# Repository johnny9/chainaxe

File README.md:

# Chainaxe

ESP32-S3 replacement control board for Antminer S19 hashboards. It drops into the stock
control-board position: the outline, mounting holes and connector positions follow a measured
drawing of the original S19 controller, and it talks to up to three hashboards over the standard
18-pin data cables.

## Board at a glance

- 110 x 100 mm, 6 layers, 1.6 mm, ENIG
- ESP32-S3-WROOM-1 (N16R8); console and flashing over native USB-C
- 3 hashboard data headers (2x9, 2.0 mm), one ESP32 UART each, plus shared I2C
- 4 fan headers (4.2 mm 2x2, or 2.54 mm 4-pin), PWM driven directly from the ESP32 and tach
  read back through PCNT
- 12 V input with reverse protection; 12 V fan bus and ground return as copper pours
- Antminer PSU control header (I2C + PSU_EN)
- On-board 3.3 V from a TPSM861253 buck module
- RESET and BOOT buttons for development

Full pinout, GPIO map and design notes: [boards/chainaxe/README.md](boards/chainaxe/README.md).

## Repository layout

| Path | What |
|---|---|
| `boards/chainaxe/` | KiCad project (schematic, PCB, local symbol and footprint libraries) |
| `mfg/assembly/` | BOM and pick-and-place files for assembly |
| `extra/outline/` | Measured S19 control-board drawing and the board outline DXF |
| `extra/axe_logo/` | Generator for the Chainaxe silkscreen icon |
| `extra/scripts/` | Helper scripts used while building the board |
| `docs/images/` | Board renders |

## Bottom

## Licence

Licensed under the CERN Open Hardware Licence Version 2 - Strongly Reciprocal
(CERN-OHL-S-2.0); see [LICENSE](LICENSE).

## Credits

Derived from [skot/bitcrane](https://github.com/skot/bitcrane) for the hashboard interface (used
under CERN-OHL-S-2.0 with the author's permission) and
[bitaxeorg/BitaxeGT](https://github.com/bitaxeorg/BitaxeGT) for the ESP32-S3 section.

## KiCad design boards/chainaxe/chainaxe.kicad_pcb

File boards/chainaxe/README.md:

# Chainaxe control board v0.1

ESP32-S3 Antminer hashboard controller. Outline, mounting holes and connector positions follow a
measured drawing of the stock S19 control board (110 x 100 mm, 6 layers; see extra/outline/),
with a BitaxeGT-style ESP32-S3-WROOM-1 in place of the Bitcrane's FTDI USB bridge.

Derived from [skot/bitcrane](https://github.com/skot/bitcrane) and
[bitaxeorg/BitaxeGT](https://github.com/bitaxeorg/BitaxeGT). Licensed CERN-OHL-S-2.0 (see the
LICENSE at the repository root).

## Connectors (same places as the stock S19 control board)

| Ref | What |
|---|---|
| J2 / J9 / J10 | Hashboard 0 / 1 / 2 data cable, Antminer 18-pin 2x9 2.0 mm |
| J4-J7, J14-J17 | Fans 1-4, 2.54 mm 4-pin or 4.2 mm 2x2 (populate one per fan) |
| J3 | 12 V in (6-pin 4.2 mm), reverse-protected by Q1 (NTMFS002P03P8Z, 1.4 mOhm) |
| J1 | Antminer PSU control, 2x3 2.0 mm (I2C + PSU_EN) |
| J11 | USB-C: ESP32-S3 native USB (flashing + console). Does not power the board. |

## ESP32-S3 GPIO map

Three hashboard UARTs: UART0, UART1 and UART2 routed through the GPIO matrix to any pins below.
The console is on USB-Serial-JTAG, so UART0's default pins (GPIO43/44) are left unused.

| Signal | GPIO | Signal | GPIO |
|---|---|---|---|
| HB0 TX | 48 | HB1 TX | 11 |
| HB0 RX | 47 | HB1 RX | 12 |
| HB0 RST | 14 | HB1 RST | 13 |
| HB0 PLUG | 21 | HB1 PLUG | 10 |
| HB2 TX | 39 | I2C SDA | 9 |
| HB2 RX | 40 | I2C SCL | 3 |
| HB2 RST | 41 | | |
| HB2 PLUG | 38 | PSU_EN | 18 |
| BOOT | 0 | USB D-/D+ | 19 / 20 |

| Fan | PWM GPIO (LEDC) | Tach GPIO (PCNT) |
|---|---|---|
| 1 | 15 | 42 |
| 2 | 16 | 44 |
| 3 | 17 | 2 |
| 4 | 8 | 1 |

The I2C bus is shared by the three hashboard headers and the PSU header. Each slot's A2-A0
straps (pins 6-8) are tied differently (slot 0 = 000, 1 = 001, 2 = 010) so the hashboards answer
at different addresses. The Bitcrane gives each hashboard its own bus through a PCA9546 instead.

Fans are driven directly: each fan's PWM pin is pulled low by a 2N7002K (Q2-Q5) whose gate the
ESP32 drives with 25 kHz LEDC PWM (inverted: gate high = PWM low). A 100k pull-down holds each gate
off, so with the ESP32 in reset the fans' own pull-ups run them at full speed. Tach lines keep
their 36k pull-ups and reach the ESP32 through 1k series resistors; count them with PCNT
(2 pulses per revolution). The ESP-to-fan lines run on the In2 (3V3 plane) layer.

## Power

12 V -> Q1 reverse protection (about 0.3 W at 12 A of fan load, drain tab stitched to a B.Cu
heat spreader) -> TPSM861253 module -> 3V3 (1 A) on the In2 plane.

Stackup: 6 layers (F.Cu signal, In1 GND, In2 3V3, In3 GND, In4 GND, B.Cu signal), the fab's
JLC06161H-3313 build.
Hashboard header pin 16 gets 3V3, as on the Bitcrane.

## Not yet checked on hardware

- Hashboard UARTs are driven straight at 3.3 V, the same as the Bitcrane does from its FTDI.
- Fan PWM pull-ups (R22, R23, R47, R48) go to 3V3. The Bitcrane has none: its EMC2305 drives the
  fans' PWM pins directly and relies on the fans' own pull-ups. They can be left unfitted.
- The shared hashboard I2C bus relies on the slot straps for unique addresses.
- GPIO44 (fan 2 tach) is UART0 RX at boot; harmless as an input.

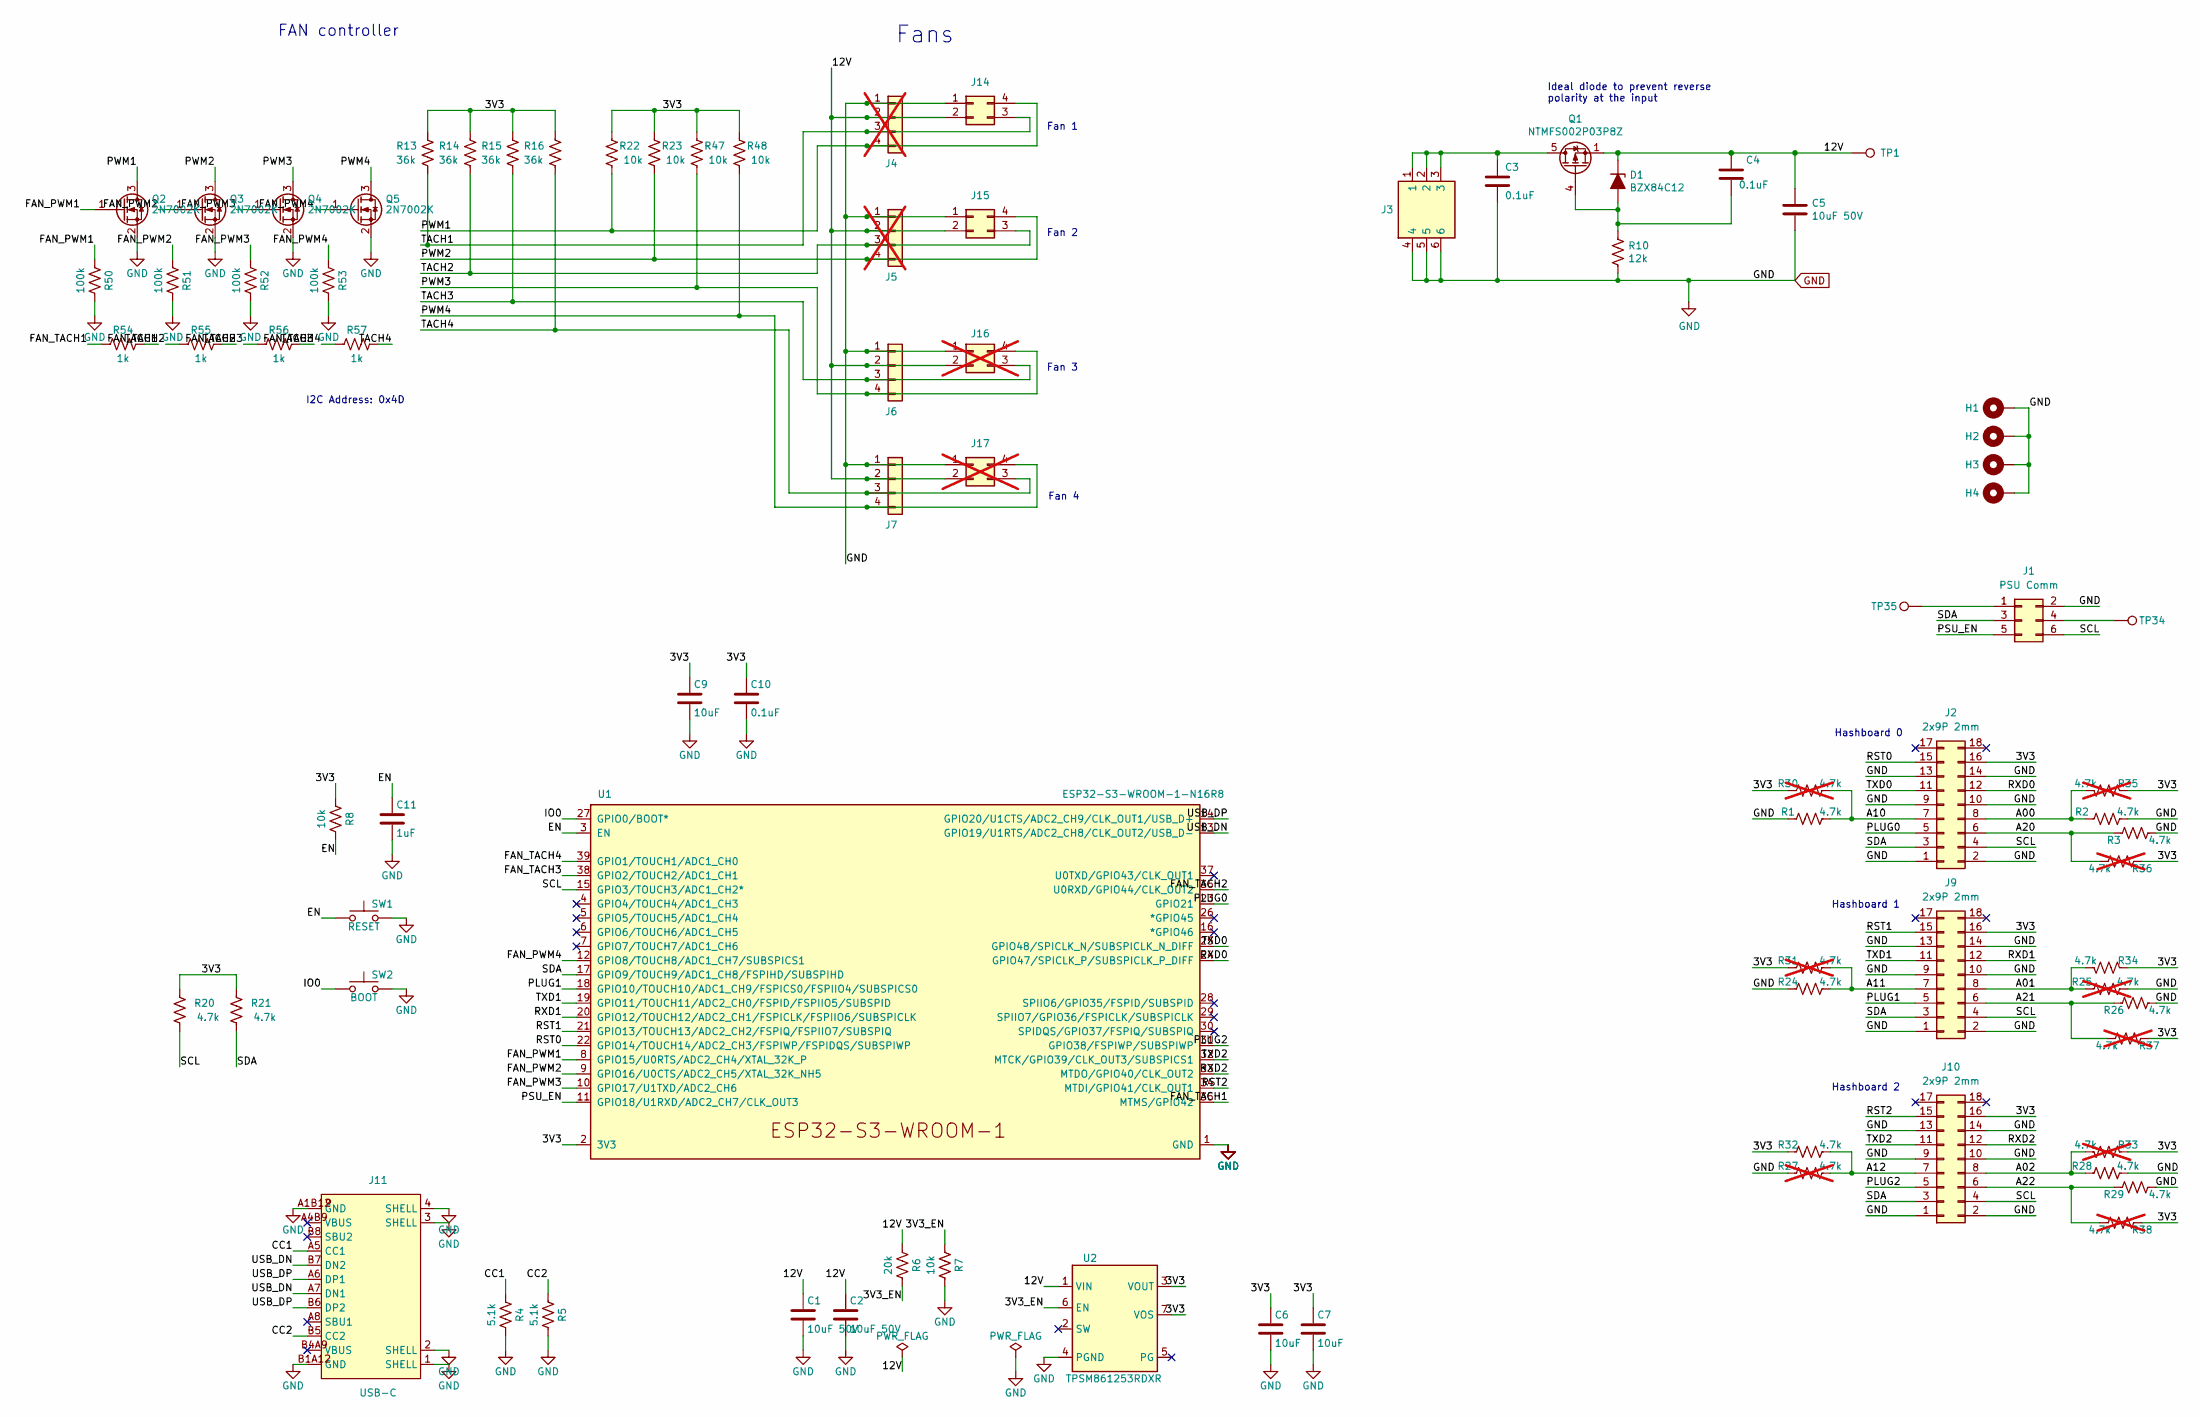
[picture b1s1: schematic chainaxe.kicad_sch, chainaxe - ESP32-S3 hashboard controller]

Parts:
C1, C2, C5: 10uF 50V; C_0805_2012Metric; MPN GRM21BR61H106KE43L; LCSC C440198
C3, C4: 0.1uF; C_0805_2012Metric; MPN CL21B104KCFNNNE; LCSC C28233
C6, C7, C9: 10uF; C_0805_2012Metric; MPN CL21A106KAYNNNE; LCSC C15850
C10: 0.1uF; C_0805_2012Metric; MPN CC0805KRX7R9BB104; LCSC C49678
C11: 1uF; C_0805_2012Metric; MPN CL21B105KBFNNNE; LCSC C28323
D1: BZX84C12; SOT-23-3_L2.9-W1.6-P1.90-LS2.8-BR; MPN BZX84C12; LCSC C19077471
H1, H2, H3, H4: MountingHole_Pad; MountingHole_3mm_Pad
J1: PSU Comm; CONN-TH_6P-P2.00_PHD-2X3A; MPN HC-PHD-2*3A; LCSC C2845614
J2, J9, J10: 2x9P 2mm; CONN-TH_X2026WV-2-09D-46SN; MPN M2026V-2x9P; LCSC C492586
J3: 0455580003; CONN-TH_50362462; MPN 50362462; LCSC C492365
J4, J5: 61900411021; CONN-TH_4P-P2.54_HCTL_HC-2510-4AW; MPN HC-2510-4AW; LCSC C2982043; not fitted
J6, J7: 61900411021; CONN-TH_4P-P2.54_HCTL_HC-2510-4AW; MPN HC-2510-4AW; LCSC C2982043
J11: USB-C; USB-C-SMD_G-SWITCH_GT-USB-7010ASV; MPN GT-USB-7010ASV; LCSC C2988369
J14, J15: 0353180420; CONN-TH_4P-P4.20_5557-2X2AW; MPN 4.2-2*2AW; LCSC C54909
J16, J17: 0353180420; CONN-TH_4P-P4.20_5557-2X2AW; MPN 4.2-2*2AW; LCSC C54909; not fitted
Q1: NTMFS002P03P8Z; onsemi_DFN5_5x6_SO-8FL; MPN NTMFS002P03P8ZT1G; LCSC C2902170
Q2, Q3, Q4, Q5: 2N7002K; SOT-23; MPN 2N7002K; LCSC C22379475
R1, R2, R3, R20, R21, R24, R26, R28, R29, R32, R34: 4.7k; R_0805_2012Metric; MPN 0805W8F4701T5E; LCSC C17673
R4, R5: 5.1k; R_0805_2012Metric; MPN 0805W8F5101T5E; LCSC C27834
R6: 20k; R_0805_2012Metric; MPN 0805W8F2002T5E; LCSC C4328
R7, R8, R22, R23, R47, R48: 10k; R_0805_2012Metric; MPN 0805W8F1002T5E; LCSC C17414
R10: 12k; R_0805_2012Metric; MPN 0805W8F1202T5E; LCSC C17444
R13, R14, R15, R16: 36k; R_0805_2012Metric; MPN 0805W8F3602T5E; LCSC C4360
R25, R27, R30, R31, R33, R35, R36, R37, R38: 4.7k; R_0805_2012Metric; MPN 0805W8F4701T5E; LCSC C17673; not fitted
R50, R51, R52, R53: 100k; R_0805_2012Metric; MPN 0805W8F1003T5E; LCSC C149504
R54, R55, R56, R57: 1k; R_0805_2012Metric; MPN 0805W8F1001T5E; LCSC C17513
SW1: RESET; SW_Push_1P1T_XKB_TS-1187A; MPN TS-1187A-B-A-B; LCSC C318884
SW2: BOOT; SW_Push_1P1T_XKB_TS-1187A; MPN TS-1187A-B-A-B; LCSC C318884
TP1, TP34, TP35: TestPoint; TestPoint_Pad_D1.5mm
U1: ESP32-S3-WROOM-1-N16R8; ESP32-S3-WROOM-1; MPN ESP32-S3-WROOM-1-N16R8; LCSC C2913202
U2: TPSM861253RDXR; TPSM863257RDX; MPN TPSM861253RDXR; LCSC C31183817

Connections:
/3V3: C6.1, C7.1, C9.1, C10.1, J2.16, J9.16, J10.16, R8.1, R13.1, R14.1, R15.1, R16.1, R20.2, R21.2, R22.2, R23.2, R30.1, R31.1, R32.1, R33.1, R34.1, R35.1, R36.1, R37.1, R38.1, R47.2, R48.2, U1.2 (3V3), U2.3 (VOUT), U2.7 (VOS)
/3V3_EN: R6.2, R7.1, U2.6 (EN)
/12V: C1.1, C2.1, C4.1, C5.1, D1.3 (K), J4.2, J5.2, J6.2, J7.2, J14.2, J15.2, J16.2, J17.2, Q1.1 (S), Q1.2 (S), Q1.3 (S), R6.1, TP1.1, U2.1 (VIN)
/A00: J2.8, R2.1, R35.2
/A01: J9.8, R25.1, R34.2
/A02: J10.8, R28.1, R33.2
/A10: J2.7, R1.2, R30.2
/A11: J9.7, R24.2, R31.2
/A12: J10.7, R27.2, R32.2
/A20: J2.6, R3.1, R36.2
/A21: J9.6, R26.1, R37.2
/A22: J10.6, R29.1, R38.2
/CC1: J11.A5 (CC1), R4.1
/CC2: J11.B5 (CC2), R5.1
/EN: C11.1, R8.2, SW1.1, U1.3 (EN)
/FAN_PWM1: Q2.1 (G), R50.1, U1.8 (GPIO15/U0RTS/ADC2_CH4/XTAL_32K_P)
/FAN_PWM2: Q3.1 (G), R51.1, U1.9 (GPIO16/U0CTS/ADC2_CH5/XTAL_32K_NH5)
/FAN_PWM3: Q4.1 (G), R52.1, U1.10 (GPIO17/U1TXD/ADC2_CH6)
/FAN_PWM4: Q5.1 (G), R53.1, U1.12 (GPIO8/TOUCH8/ADC1_CH7/SUBSPICS1)
/FAN_TACH1: R54.1, U1.35 (MTMS/GPIO42)
/FAN_TACH2: R55.1, U1.36 (U0RXD/GPIO44/CLK_OUT2)
/FAN_TACH3: R56.1, U1.38 (GPIO2/TOUCH2/ADC1_CH1)
/FAN_TACH4: R57.1, U1.39 (GPIO1/TOUCH1/ADC1_CH0)
/IO0: SW2.1, U1.27 (GPIO0/BOOT*)
/PLUG0: J2.5, U1.23 (GPIO21)
/PLUG1: J9.5, U1.18 (GPIO10/TOUCH10/ADC1_CH9/FSPICS0/FSPIIO4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)
/PLUG2: J10.5, U1.31 (GPIO38/FSPIWP/SUBSPIWP)
/PSU_EN: J1.5, U1.11 (GPIO18/U1RXD/ADC2_CH7/CLK_OUT3)
/PWM1: J4.4, J14.4, Q2.3 (D), R22.1
/PWM2: J5.4, J15.4, Q3.3 (D), R23.1
/PWM3: J6.4, J16.4, Q4.3 (D), R47.1
/PWM4: J7.4, J17.4, Q5.3 (D), R48.1
/RST0: J2.15, U1.22 (GPIO14/TOUCH14/ADC2_CH3/FSPIWP/FSPIDQS/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)
/RST1: J9.15, U1.21 (GPIO13/TOUCH13/ADC2_CH2/FSPIQ/FSPIIO7/S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)
/RST2: J10.15, U1.34 (MTDI/GPIO41/CLK_OUT1)
/RXD0: J2.12, U1.24 (GPIO47/SPICLK_P/SUBSPICLK_P_DIFF)
/RXD1: J9.12, U1.20 (GPIO12/TOUCH12/ADC2_CH1/FSPICLK/FSPIIO6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)
/RXD2: J10.12, U1.33 (MTDO/GPIO40/CLK_OUT2)
/SCL: J1.6, J2.4, J9.4, J10.4, R20.1, U1.15 (GPIO3/TOUCH3/ADC1_CH2*)
/SDA: J1.3, J2.3, J9.3, J10.3, R21.1, U1.17 (GPIO9/TOUCH9/ADC1_CH8/FSPIHD/SUBSPIHD)
/TACH1: J4.3, J14.3, R13.2, R54.2
/TACH2: J5.3, J15.3, R14.2, R55.2
/TACH3: J6.3, J16.3, R15.2, R56.2
/TACH4: J7.3, J17.3, R16.2, R57.2
/TXD0: J2.11, U1.25 (GPIO48/SPICLK_N/SUBSPICLK_N_DIFF)
/TXD1: J9.11, U1.19 (GPIO11/TOUCH11/ADC2_CH0/FSPID/FSPIIO5/S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)
/TXD2: J10.11, U1.32 (MTCK/GPIO39/CLK_OUT3/SUBSPICS1)
/USB_DN: J11.A7 (DN1), J11.B7 (DN2), U1.13 (GPIO19/U1RTS/ADC2_CH8/CLK_OUT2/USB_D-)
/USB_DP: J11.A6 (DP1), J11.B6 (DP2), U1.14 (GPIO20/U1CTS/ADC2_CH9/CLK_OUT1/USB_D+)
GND: C1.2, C2.2, C3.2, C5.2, C6.2, C7.2, C9.2, C10.2, C11.2, H1.1, H2.1, H3.1, H4.1, J1.2, J2.1, J2.2, J2.9, J2.10, J2.13, J2.14, J3.4, J3.5, J3.6, J4.1, J5.1, J6.1, J7.1, J9.1, J9.2, J9.9, J9.10, J9.13, J9.14, J10.1, J10.2, J10.9, J10.10, J10.13, J10.14, J11.1 (SHELL), J11.2 (SHELL), J11.3 (SHELL), J11.4 (SHELL), J11.A1B12 (GND), J11.B1A12 (GND), J14.1, J15.1, J16.1, J17.1, Q2.2 (S), Q3.2 (S), Q4.2 (S), Q5.2 (S), R1.1, R2.2, R3.2, R4.2, R5.2, R7.2, R10.2, R24.1, R25.2, R26.2, R27.1, R28.2, R29.2, R50.2, R51.2, R52.2, R53.2, SW1.2, SW2.2, U1.1 (GND), U1.40 (GND), U1.41 (GND), U2.4 (PGND)
unnamed: C3.1, J3.1, J3.2, J3.3, Q1.5 (D), Q1.6 (D), Q1.7 (D), Q1.8 (D)
unnamed: C4.2, D1.1 (A), Q1.4 (G), R10.1
unnamed: J1.1, TP35.1
unnamed: J1.4, TP34.1

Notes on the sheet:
Fan 2
Fan 3
FAN controller
Hashboard 1
I2C Address: 0x4D
Fan 4
Fans
Ideal diode to prevent reverse polarity at the input
Hashboard 2
Fan 1
Hashboard 0

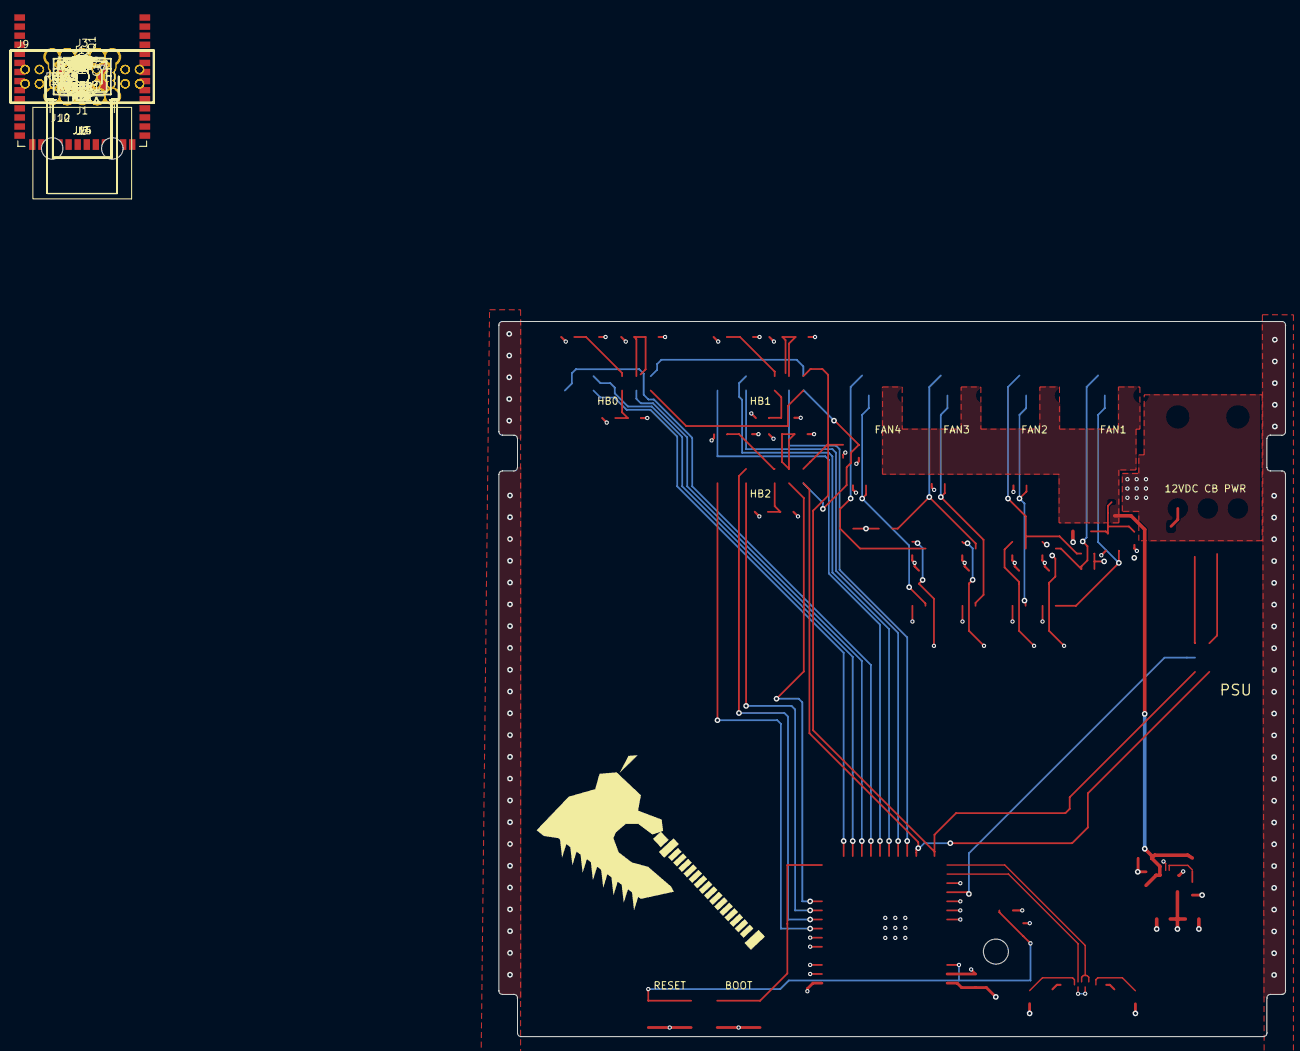
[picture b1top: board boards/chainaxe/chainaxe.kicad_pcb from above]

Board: 6 copper layers, 110.0 x 100.0 mm, 86 parts (0 on the bottom side), 54 nets.

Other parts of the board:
FID1, FID2, FID3: Fiducial; Fiducial_1mm_Mask2mm

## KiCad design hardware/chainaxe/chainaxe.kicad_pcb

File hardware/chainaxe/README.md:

# ChainAxe KiCad project

This directory contains the editable Rev A.1 KiCad baseline.

## Files

- `chainaxe.kicad_pro` — KiCad project settings and provisional net classes.
- `chainaxe.kicad_sch` — annotated preliminary schematic.
- `chainaxe.kicad_pcb` — 100 × 70 mm unrouted placement baseline.
- `chainaxe.kicad_dru` — conservative prototype rules.
- `pin-net-audit.csv` — exhaustive expected/actual connection contract for every schematic pin.
- `symbols/ChainAxe.kicad_sym` and `sym-lib-table` — project-local custom symbols.
- `ChainAxe.pretty/` and `fp-lib-table` — nine pinned project-local manufacturer-derived/audited footprints.

Open `chainaxe.kicad_pro` in KiCad 9. KiCad may update generated metadata when the project is first saved; review that diff before committing it.

The source package is structurally checked by `scripts/validate_design.py`. The exhaustive `pin-net-audit.csv` contract is independently checked against physical symbol-pin endpoints by `scripts/validate_schematic_pinmap.py`; that validator explicitly converts KiCad library Y-up coordinates to schematic Y-down coordinates. `scripts/validate_pcb_geometry.py` checks different-net pad intersections, NPTH/copper conflicts, body/courtyard collisions, and undocumented edge overhangs. All three are dependency-free CI checks. This build environment does not include `kicad-cli`, so a local KiCad 9 ERC/DRC run remains mandatory before any fabrication export; none of the source validators replaces it.

Fan startup is hardware-defined: R105 holds `FAN_ARM` low, while R106–R109 hold the four EMC2305 PWM inputs to U8 low. This keeps the open-drain fan sinks released (the supported-fan full-speed-safe state) even if firmware asserts `FAN_ARM` before configuring the EMC2305. J30's audit enumerates every USB4105-GF-A signal/power contact; its A9/B9 VBUS and A12/B12 ground contacts are stacked on their shared logical nets. The official footprint numbers all four conductive shell stakes as `S1`, so one audited `S1` pin owns that common shell net.

C112 is the populated 100 nF USBLC6 VBUS bypass and must sit directly beside U9 pins 5/2. C3, the optional 220 µF 3V3 bulk footprint, is native DNP until AP64501 loop and load-transient validation proves an appropriate bulk value.

## Design status

This is an engineering-entry design, not an order-ready board. The schematic and PCB capture the intended architecture, safe startup states, connector map, and major candidate parts. The following remain release blockers:

- real-mating-part fit and keyed circuit-view checks for J1, J2–J6, J10, and USB-C; J6's exact connector/part remains a stop-order choice;
- fan current, inrush, reverse-polarity FET, connector, copper, and thermal calculations;
- AP64501 feedback, compensation, inductor, capacitance, and thermal verification;
- ESD/TVS clamping analysis and final ordering codes;
- exact first hashboard SKU/profile, including RESET policy and local voltage-off behavior;
- KiCad ERC, PCB synchronization, routing, stack-up impedance calculation, and DRC; and
- JLCPCB assembly preview, BOM/CPL reconciliation, and first-article review.

Do not generate production Gerbers from this baseline without closing the stop-order gates in `../../design-review-checklist.md`.

## PCB intent

The PCB is intentionally unrouted. The fan-current band stays at the top/right edge, the J10 interface lane stays at the left edge, and the ESP32-S3 antenna faces the bottom board edge with a 15 mm keepout. The `USB_90OHM_PLACEHOLDER` and `FAN_POWER_PROVISIONAL` net classes are reminders, not validated geometries.

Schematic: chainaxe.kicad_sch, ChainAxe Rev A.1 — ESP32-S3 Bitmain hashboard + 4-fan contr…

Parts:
C1, C2, C100, C102: 100n; C_0402_1005Metric
C3: 220uF LOW ESR — DNP POST-LOOP VALIDATION; CP_Elec_8x10.2; not fitted
C15: 100n 25V BOOTSTRAP; C_0402_1005Metric
C16: 10n SOFT START; C_0402_1005Metric
C17: 2.7n COMP — DS41980 TABLE 1; C_0402_1005Metric
C18: 56p COMP POLE DNP — DS41980 TABLE 1 C6; C_0402_1005Metric; not fitted
C20, C21: 470uF 25V LOW ESR; CP_Radial_D10.0mm_P5.00mm
C50: 1n CT TO VIN — PROVISIONAL; C_0402_1005Metric
C51: 1u U5 VIN BYPASS; C_0402_1005Metric
C52: 1u HB_3V3 LOCAL; C_0402_1005Metric
C70: 10n; C_0402_1005Metric
C80: 100n U6 VCCA; C_0402_1005Metric
C81: 100n U6 VCCB; C_0402_1005Metric
C101: 1u; C_0805_2012Metric
C103: 100n TMUX VDD; C_0402_1005Metric
C104: 100n U12 VCC; C_0402_1005Metric
C110: 1u EN delay; C_0402_1005Metric
C111: 1n 2kV SHIELD; C_0805_2012Metric
C112: 100nF 50V X7R — U9 VBUS BYPASS; C_0402_1005Metric; LCSC C307331
C200, C201, C202, C203: 100p TACH FILTER DNP; C_0402_1005Metric; not fitted
CIN1, CIN2, CIN3, CIN4: 10uF 50V X7R; C_1210_3225Metric
COUT1, COUT2, COUT3: 22uF 10V X7R; C_0805_2012Metric
D1: SS14 1A 40V; D_SMA; MPN SS14
D2, D3: SS14 1A 40V; D_SMA
D4: SMBJ13A PROVISIONAL; D_SMB; MPN SMBJ13A
D5: SMBJ18CA BIDIRECTIONAL PROVISIONAL; D_SMB; MPN SMBJ18CA
J1: FAN INPUT 12V ONLY — 0455580003; 0455580003_THT; MPN 0455580003; LCSC C492365
J2: FAN 1 — G 12 T P; 0353180420_THT; MPN 0353180420; LCSC C54909
J3: FAN 2 — G 12 T P; 0353180420_THT; MPN 0353180420; LCSC C54909
J4: FAN 3 — G 12 T P; 0353180420_THT; MPN 0353180420; LCSC C54909
J5: FAN 4 — G 12 T P; 0353180420_THT; MPN 0353180420; LCSC C54909
J6: LOGIC IN 12–15V — KEYED TBD; Molex_Micro-Fit_3.0_43650-0200_1x02_P3.00mm_Horizontal
J10: BITMAIN HASHBOARD DATA 2x9 / 18 POS; PM200-2-09-W-4.3_THT; MPN PM200-2-09-W-4.3; LCSC C3012192
J30: USB4105-GF-A — USB2 DEVICE; USB4105-GF-A; MPN USB4105-GF-A; LCSC C2988369
JP1: FAN_TO_LOGIC — DNP; SolderJumper-2_P1.3mm_Open_Pad1.0x1.5mm; not fitted
L1: 3.3uH SRP5030T-3R3M; L_Bourns-SRP5030TA_5.7x5.2mm; MPN SRP5030T-3R3M; LCSC C189931
Q1, Q2, Q3, Q4: 2N7002 OPEN-DRAIN PWM; SOT-23; MPN 2N7002; LCSC C8545
Q5, Q6: DMP3013SFV-7 PROVISIONAL; PowerDI3333-8_DMP3013SFV; MPN DMP3013SFV-7; LCSC C264098
R50: 100k; R_0402_1005Metric
R51: 100R QOD LINK — PROVISIONAL; R_0402_1005Metric
R60: 12k 1%; R_0402_1005Metric
R65: 10.5k COMP — DS41980 TABLE 1; R_0402_1005Metric
R70: 100k 1%; R_0402_1005Metric
R71: 27k 1%; R_0402_1005Metric
R80: 100k OE DISABLE; R_0402_1005Metric
R81: 33R TX; R_0402_1005Metric
R82: 33R RX PROVISIONAL; R_0402_1005Metric
R83: 100k ESP-SIDE PLUG PULLDOWN; R_0402_1005Metric
R84: 100k EN OFF; R_0402_1005Metric
R85, R86, R87, R88, R100, R101, R102: 4.7k; R_0402_1005Metric
R89: 10k RESET OE DISABLE; R_0402_1005Metric
R90: RESET_ENABLE_LINK — 33R DNP FOR S21; R_0402_1005Metric; not fitted
R91: 100k RESET BIAS-UP DNP; R_0402_1005Metric; not fitted
R92: 100k RESET BIAS-DN DNP; R_0402_1005Metric; not fitted
R93, R95, R97: 4.7k DEFAULT LOW; R_0402_1005Metric
R94, R96, R98: 0R HIGH OPTION DNP; R_0402_1005Metric; not fitted
R103: 22k CLK STRAP; R_0402_1005Metric
R104: 33k ADDR STRAP; R_0402_1005Metric
R105: 100k ARM OFF; R_0402_1005Metric
R106: 100k 1% PWM1 SAFE LOW; R_0402_1005Metric
R107: 100k 1% PWM2 SAFE LOW; R_0402_1005Metric
R108: 100k 1% PWM3 SAFE LOW; R_0402_1005Metric
R109: 100k 1% PWM4 SAFE LOW; R_0402_1005Metric
R110: 10k EN pull-up; R_0402_1005Metric
R111: 10k BOOT pull-up; R_0402_1005Metric
R112: 5.1k CC1; R_0402_1005Metric; LCSC C25905
R113: 5.1k CC2; R_0402_1005Metric; LCSC C25905
R114: 22R USB D+; R_0402_1005Metric; LCSC C25105
R115: 22R USB D-; R_0402_1005Metric; LCSC C25105
R116: 1M SHIELD; R_0402_1005Metric
R200, R203, R206, R209: 100k GATE OFF; R_0402_1005Metric
R201, R204, R207, R210: 36k TACH PULLUP; R_0402_1005Metric; LCSC C137999
RFB1: 69.8k 1% — DS41980 TABLE 1; R_0402_1005Metric
RFB2: 22.1k 1% — DS41980 TABLE 1; R_0402_1005Metric
SW1: BOOT; SW_SPST_CK_RS282G05A3; MPN CS1213AGF260; LCSC C5578986
SW2: RESET; SW_SPST_CK_RS282G05A3; MPN CS1213AGF260; LCSC C5578986
TP1: FAN_12V_RAW; TestPoint_Pad_D1.0mm
TP2: FAN_12V; TestPoint_Pad_D1.0mm
TP3: VIN_LOGIC_12_15; TestPoint_Pad_D1.0mm
TP4: LOGIC_IN; TestPoint_Pad_D1.0mm
TP5, TP13: 3V3; TestPoint_Pad_D1.0mm
TP6: HB_3V3; TestPoint_Pad_D1.0mm
TP7: RAIL_MON; TestPoint_Pad_D1.0mm
TP8: DBG_TX; TestPoint_Pad_D1.0mm
TP9: DBG_RX; TestPoint_Pad_D1.0mm
TP10: EXP_GPIO5; TestPoint_Pad_D1.0mm
TP11: EXP_GPIO6; TestPoint_Pad_D1.0mm
TP12: GND; TestPoint_Pad_D1.0mm
TP14: FAN_PWM1; TestPoint_Pad_D1.0mm
TP15: FAN_TACH1; TestPoint_Pad_D1.0mm
TP16: FAN_PWM2; TestPoint_Pad_D1.0mm
TP17: FAN_TACH2; TestPoint_Pad_D1.0mm
TP18: FAN_PWM3; TestPoint_Pad_D1.0mm
TP19: FAN_TACH3; TestPoint_Pad_D1.0mm
TP20: FAN_PWM4; TestPoint_Pad_D1.0mm
TP21: FAN_TACH4; TestPoint_Pad_D1.0mm
TP22: FAN_ARM; TestPoint_Pad_D1.0mm
TP23: FAN_ALERT_N; TestPoint_Pad_D1.0mm
TP24: FAN_SDA; TestPoint_Pad_D1.0mm
TP25: FAN_SCL; TestPoint_Pad_D1.0mm
TP26: USB_VBUS; TestPoint_Pad_D1.0mm
TP27: HB_RESET_CMD; TestPoint_Pad_D1.0mm
TP28: HB_IO_PWR_EN; TestPoint_Pad_D1.0mm
TP29: HB_TX; TestPoint_Pad_D1.0mm
TP30: HB_RX; TestPoint_Pad_D1.0mm
TP31: HB_PLUG; TestPoint_Pad_D1.0mm
TP32: HB_SDA; TestPoint_Pad_D1.0mm
TP33: HB_SCL; TestPoint_Pad_D1.0mm
TP34: HB_RESET; TestPoint_Pad_D1.0mm
TP35: HB_XLAT_OE_N; TestPoint_Pad_D1.0mm
TP36: HB_I2C_EN; TestPoint_Pad_D1.0mm
TP37: HB_RESET_OE_N; TestPoint_Pad_D1.0mm
U1: ESP32-S3-WROOM-1-N16R8; ESP32-S3-WROOM-1_v1.8; MPN ESP32-S3-WROOM-1-N16R8; LCSC C2913202
U2: EMC2305-1-AP-TR; EMC2305_QFN16_4x4_P0.65_EP2.2; MPN EMC2305-1-AP-TR; LCSC C621415
U3: AP64501SP-13 — 3V3 BUCK PROVISIONAL; AP64501_SO8EP; MPN AP64501SP-13; LCSC C2071517
U5: TPS22917DBVR — HB 3V3 SWITCH; SOT-23-6; MPN TPS22917DBVR; LCSC C2681320
U6: SN74AXC4T774PWR — UART/PLUG GATED; TSSOP-16_4.4x5mm_P0.65mm; MPN SN74AXC4T774PWR; LCSC C1849453
U7: TMUX1511PWR — GATED HB I2C; TSSOP-14_4.4x5mm_P0.65mm; MPN TMUX1511PWR; LCSC C2866750
U8: SN74LVC126APWR — FAN PWM ARM; TSSOP-14_4.4x5mm_P0.65mm; MPN SN74LVC126APWR
U9: USBLC6-2SC6; SOT-23-6; MPN USBLC6-2SC6; LCSC C7519
U10, U11, U13: TPD4E05U06DQAR; TI_DQA0010A_USON10_2.5x1.0_P0.5; MPN TPD4E05U06DQAR; LCSC C138714
U12: SN74LVC1G125DBVR — RESET GATE; SOT-23-5; MPN SN74LVC1G125DBVR
ZD1: BZX84C12LT1G 12V VGS clamp; SOT-23; MPN BZX84C12LT1G; LCSC C82475

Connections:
3V3: C1.1, C2.1, C3.1, C50.2, C51.1, C80.1, C100.1, C101.1, C102.1, COUT1.1, COUT2.1, COUT3.1, L1.2, R80.2, R85.2, R86.2, R89.2, R100.2, R101.2, R102.2, R103.2, R104.2, R110.1, R111.1, R201.2, R204.2, R207.2, R210.2, RFB1.1, TP5.1, TP13.1, U1.2 (3V3), U2.3 (VDD), U5.1 (VIN), U6.1 (DIR1), U6.8 (DIR4), U6.16 (VCCA), U8.14 (VCC)
BOOT_N: R111.2, SW1.1, U1.27 (GPIO0/BOOT*)
BUCK_BST: C15.1, U3.1 (BST)
BUCK_COMP: C18.1, R65.1, U3.6 (COMP)
BUCK_COMP_RC: C17.1, R65.2
BUCK_FB: RFB1.2, RFB2.1, U3.5 (FB)
BUCK_SS: C16.1, U3.4 (SS)
BUCK_SW: C15.2, L1.1, U3.8 (SW)
DBG_RX: TP9.1, U1.36 (U0RXD/GPIO44/CLK_OUT2)
DBG_TX: TP8.1, U1.37 (U0TXD/GPIO43/CLK_OUT1)
EMC_ADDR: R104.1, U2.4 (ADDR_SEL)
EMC_CLK: R103.1, U2.11 (CLK)
EMC_PWM1: R106.1, U2.5 (PWM1), U8.2 (1A)
EMC_PWM2: R107.1, U2.7 (PWM2), U8.5 (2A)
EMC_PWM3: R108.1, U2.9 (PWM3), U8.9 (3A)
EMC_PWM4: R109.1, U2.13 (PWM4), U8.12 (4A)
ESP_EN: C110.1, R110.2, SW2.1, U1.3 (EN)
EXP_GPIO5: TP10.1, U1.5 (GPIO5/TOUCH5/ADC1_CH4)
EXP_GPIO6: TP11.1, U1.6 (GPIO6/TOUCH6/ADC1_CH5)
FAN_12V: C20.1, C21.1, D4.1 (K), J2.2, J3.2, J4.2, J5.2, JP1.1 (A), Q5.1 (SOURCE), Q5.2 (SOURCE), Q5.3 (SOURCE), Q6.1 (SOURCE), Q6.2 (SOURCE), Q6.3 (SOURCE), R70.1, TP2.1, ZD1.3 (K)
FAN_12V_RAW: J1.4, J1.5, J1.6, Q5.5 (DRAIN), Q5.6 (DRAIN), Q5.7 (DRAIN), Q5.8 (DRAIN), Q6.5 (DRAIN), Q6.6 (DRAIN), Q6.7 (DRAIN), Q6.8 (DRAIN), TP1.1
FAN_ALERT_N: R102.1, TP23.1, U1.21 (GPIO13/TOUCH13/ADC2_CH2/FSPIQ/FSPIIO7/S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), U2.12 (~ALERT)
FAN_ARM: R105.1, TP22.1, U1.12 (GPIO8/TOUCH8/ADC1_CH7/SUBSPICS1), U8.1 (1OE), U8.4 (2OE), U8.10 (3OE), U8.13 (4OE)
FAN_GATE1: Q1.1 (G), R200.1, U8.3 (1Y)
FAN_GATE2: Q2.1 (G), R203.1, U8.6 (2Y)
FAN_GATE3: Q3.1 (G), R206.1, U8.8 (3Y)
FAN_GATE4: Q4.1 (G), R209.1, U8.11 (4Y)
FAN_PWM1: J2.4, Q1.3 (D), TP14.1
FAN_PWM2: J3.4, Q2.3 (D), TP16.1
FAN_PWM3: J4.4, Q3.3 (D), TP18.1
FAN_PWM4: J5.4, Q4.3 (D), TP20.1
FAN_RPP_GATE: Q5.4 (GATE), Q6.4 (GATE), R60.1, ZD1.1 (A)
FAN_SCL: R101.1, TP25.1, U1.25 (GPIO48/SPICLK_N/SUBSPICLK_N_DIFF), U2.2 (SMCLK)
FAN_SDA: R100.1, TP24.1, U1.24 (GPIO47/SPICLK_P/SUBSPICLK_P_DIFF), U2.1 (SMDATA)
FAN_TACH1: C200.1, J2.3, R201.1, TP15.1, U2.6 (TACH1)
FAN_TACH2: C201.1, J3.3, R204.1, TP17.1, U2.8 (TACH2)
FAN_TACH3: C202.1, J4.3, R207.1, TP19.1, U2.10 (TACH3)
FAN_TACH4: C203.1, J5.3, R210.1, TP21.1, U2.14 (TACH4)
FAN_TO_LOGIC_FEED: D2.2 (A), JP1.2 (B)
GND: C1.2, C2.2, C3.2, C16.2, C17.2, C18.2, C20.2, C21.2, C51.2, C52.2, C70.2, C80.2, C81.2, C100.2, C101.2, C102.2, C103.2, C104.2, C110.2, C111.2, C112.2, C200.2, C201.2, C202.2, C203.2, CIN1.2, CIN2.2, CIN3.2, CIN4.2, COUT1.2, COUT2.2, COUT3.2, D4.2 (A), D5.2 (A2), J1.1, J1.2, J1.3, J2.1, J3.1, J4.1, J5.1, J6.2, J10.1, J10.2, J10.9, J10.10, J10.13, J10.14, J30.A1 (GND), J30.A12 (GND), J30.B1 (GND), J30.B12 (GND), Q1.2 (S), Q2.2 (S), Q3.2 (S), Q4.2 (S), R50.2, R60.2, R71.2, R83.2, R84.2, R92.2, R93.2, R95.2, R97.2, R105.2, R106.2, R107.2, R108.2, R109.2, R112.2, R113.2, R116.2, R200.2, R203.2, R206.2, R209.2, RFB2.2, SW1.2, SW2.2, TP12.1, U1.1 (GND), U1.40 (GND), U1.41 (GND), U2.17 (GND), U3.7 (GND), U3.9 (EP), U5.2 (GND), U6.2 (DIR2), U6.6 (A4), U6.7 (DIR3), U6.10 (GND), U7.7 (GND), U7.10 (SEL3), U7.13 (SEL4), U8.7 (GND), U9.2 (GND), U10.3 (GND), U10.8 (GND), U11.3 (GND), U11.8 (GND), U12.3 (GND), U13.3 (GND), U13.8 (GND)
HB_3V3: C52.1, C81.1, C103.1, C104.1, J10.16, R51.1, R87.2, R88.2, R91.2, R94.2, R96.2, R98.2, TP6.1, U5.6 (VOUT), U6.15 (VCCB), U7.14 (VDD), U12.5 (VCC)
HB_3V3_CT: C50.1, U5.4 (CT)
HB_A0: J10.8, R93.1, R94.1, U11.2 (D1-)
HB_A1: J10.7, R95.1, R96.1, U11.1 (D1+)
HB_A2: J10.6, R97.1, R98.1, U10.5 (D2-)
HB_I2C_EN: R84.1, TP36.1, U1.17 (GPIO9/TOUCH9/ADC1_CH8/FSPIHD/SUBSPIHD), U7.1 (SEL1), U7.4 (SEL2)
HB_IO_PWR_EN: R50.1, TP28.1, U1.18 (GPIO10/TOUCH10/ADC1_CH9/FSPICS0/FSPIIO4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), U5.3 (ON)
HB_PLUG: J10.5, TP31.1, U6.12 (B3), U10.4 (D2+)
HB_PLUG_3V3: R83.1, U1.20 (GPIO12/TOUCH12/ADC2_CH1/FSPICLK/FSPIIO6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), U6.5 (A3)
HB_QOD: R51.2, U5.5 (QOD)
HB_RESET: J10.15, R90.2, R91.1, R92.1, TP34.1, U13.1 (D1+)
HB_RESET_CMD: TP27.1, U1.39 (GPIO1/TOUCH1/ADC1_CH0), U12.2 (A)
HB_RESET_DRV: R90.1, U12.4 (Y)
HB_RESET_OE_N: R89.1, TP37.1, U1.4 (GPIO4/TOUCH4/ADC1_CH3), U12.1 (OE_N)
HB_RX: J10.12, R82.1, TP30.1, U11.5 (D2-)
HB_RX_3V3: U1.11 (GPIO18/U1RXD/ADC2_CH7/CLK_OUT3), U6.4 (A2)
HB_RX_BUF: R82.2, U6.13 (B2)
HB_SCL: J10.4, R87.1, TP33.1, U7.3 (D1), U10.2 (D1-)
HB_SCL_3V3: R85.1, U1.23 (GPIO21), U7.2 (S1)
HB_SDA: J10.3, R88.1, TP32.1, U7.6 (D2), U10.1 (D1+)
HB_SDA_3V3: R86.1, U1.22 (GPIO14/TOUCH14/ADC2_CH3/FSPIWP/FSPIDQS/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), U7.5 (S2)
HB_TX: J10.11, R81.2, TP29.1, U11.4 (D2+)
HB_TX_3V3: U1.10 (GPIO17/U1TXD/ADC2_CH6), U6.3 (A1)
HB_TX_BUF: R81.1, U6.14 (B1)
HB_XLAT_OE_N: R80.1, TP35.1, U1.7 (GPIO7/TOUCH7/ADC1_CH6), U6.9 (OE)
LOGIC_IN: CIN1.1, CIN2.1, CIN3.1, CIN4.1, D1.1 (K), D2.1 (K), D3.1 (K), TP4.1, U3.2 (VIN), U3.3 (EN)
RAIL_MON: C70.1, R70.2, R71.1, TP7.1, U1.19 (GPIO11/TOUCH11/ADC2_CH0/FSPID/FSPIIO5/S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)
USB_CC1: J30.A5 (CC1), R112.1
USB_CC2: J30.B5 (CC2), R113.1
USB_DN: R115.2, U1.13 (GPIO19/U1RTS/ADC2_CH8/CLK_OUT2/USB_D-)
USB_DN_CONN: J30.A7 (D-), J30.B7 (D-), U9.3 (I/O2)
USB_DN_PROT: R115.1, U9.4 (I/O2)
USB_DP: R114.2, U1.14 (GPIO20/U1CTS/ADC2_CH9/CLK_OUT1/USB_D+)
USB_DP_CONN: J30.A6 (D+), J30.B6 (D+), U9.1 (I/O1)
USB_DP_PROT: R114.1, U9.6 (I/O1)
USB_SHIELD: C111.1, J30.S1 (SHIELD), R116.1
USB_VBUS: C112.1, D3.2 (A), J30.A4 (VBUS), J30.A9 (VBUS), J30.B4 (VBUS), J30.B9 (VBUS), TP26.1, U9.5 (VBUS)
VIN_LOGIC_12_15: D1.2 (A), D5.1 (A1), J6.1, TP3.1

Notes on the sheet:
CHAINAXE REV A.1 — PRELIMINARY / NOT FOR FABRICATION
POWER + PROTECTION (J1 regulated 12V fan power; J6 controller-only 12–15V)
ESP32-S3 + USB / DEBUG
HASHBOARD CABLE INTERFACE — COMMON 2x9 / 18-POSITION FORM
FAN CONTROL — 4x ANTHAT-STYLE 12V 4-WIRE
DANGER / S21 ASSEMBLY RULE: leave R90 RESET_ENABLE_LINK OPEN/DNP. Firmware must also never enable U12. Hardware safety is not firmware-only.
SAFE STARTUP: R105 keeps FAN_ARM=0 and R106-R109 hold U8 PWM inputs low; sinks stay released/full-speed-safe. HB_3V3=OFF; U6/U7/U12 disabled or high-Z. Prove every state on hardware.
NO PSU CONTROL ON REV A.1. Hashboard core power remains external; an interface fault cannot guarantee removal of ASIC core power.
J1/fan copper is high current. External fuse required near source. Select FET count, connector, copper, and thermals from measured simultaneous startup/stall current.
FAN PROFILE RULE: supported 4-wire fans must include their own PWM pull-up. ChainAxe provides open-drain sinks only; fans needing an external pull-up are unsupported.
HASHBOARD POWER RULE: J10 pin16 HB_3V3 is controller-sourced only through U5. Never externally drive or backfeed this rail while R51 QOD is populated.
All connector drawings are mating-face views. Continuity-check pin 1, keying, fan G/12/T/P, J10 positions 17/18 NC, and shared ground before power.
PROVISIONAL/TBD: J6 selection and all connector fit checks; AP64501 compensation/magnetics; TVS ratings; FET thermals; EMC2305 straps; exact S19/S21 profile.
JLCPCB intent: 4-layer, mostly 0402/0805; extended parts accepted; J1/J2-J5/J10 hand-install. Verify fresh manufacturer-drawing footprints with 1:1 prints.
Source basis: bitaxeorg/bitaxeNaja, skot/aditBoard, skot/AntHat, and manufacturer datasheets. Independently audit every critical symbol and footprint before fabrication.

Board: 4 copper layers, 163 parts (0 on the bottom side), 78 nets, no tracks yet.

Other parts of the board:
H1, H2, H3, H4: M3; MountingHole_3.2mm_M3

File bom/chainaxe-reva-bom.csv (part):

Status,Designator,Qty,Function,Value,Manufacturer,MPN,Footprint,LCSC Part #,Assembly,Population,Notes
EXACT_CANDIDATE,U1,1,MCU module,ESP32-S3-WROOM-1-N16R8,Espressif,ESP32-S3-WROOM-1-N16R8,ChainAxe:ESP32-S3-WROOM-1_v1.8,C2913202,SMT extended,POPULATE,"Project-local footprint follows Espressif v1.8 land pattern with 3.7 mm center pad/vias and antenna keepout; verify metal-chassis strategy"
PROVISIONAL,U2,1,Four-channel fan controller,EMC2305,Microchip,EMC2305-1-AP-TR,ChainAxe:EMC2305_QFN16_4x4_P0.65_EP2.2,C621415,SMT extended,POPULATE,"AP-specific 2.2 mm exposed land with paste windowing and thermal vias; use channels 1-4; fifth channel NC"
PROVISIONAL,U3,1,3.3 V synchronous buck,AP64501,Diodes Incorporated,AP64501SP-13,ChainAxe:AP64501_SO8EP,C2071517,SMT extended,POPULATE,"Project-local Diodes land/paste/thermal-via pattern; DS41980 Table 1 starting cell is implemented; validate loop stability, transients, and thermal margin"
PROVISIONAL,L1,1,Buck inductor,3.3 uH,Bourns,SRP5030T-3R3M,Inductor_SMD:L_Bourns-SRP5030TA_5.7x5.2mm,C189931,SMT extended,POPULATE,"Recalculate saturation and RMS current for the final 3.3 V design"
PROVISIONAL,U5,1,Switched hashboard logic supply,3.3 V 2 A load switch,Texas Instruments,TPS22917DBVR,Package_TO_SOT_SMD:SOT-23-6,C2681320,SMT extended,POPULATE,"Controller sources J10 pin 16; R50 holds the switch off at reset"
PROVISIONAL,U6,1,Gated hashboard UART/PLUG interface,SN74AXC4T774,Texas Instruments,SN74AXC4T774PWR,Package_SO:TSSOP-16_4.4x5mm_P0.65mm,C1849453,SMT extended,POPULATE,"Both domains are 3.3 V; directions and OE mapping are frozen in the schematic"
EXACT_CANDIDATE,U7,1,Powered-off-protected hashboard I2C switch,TMUX1511,Texas Instruments,TMUX1511PWR,Package_SO:TSSOP-14_4.4x5mm_P0.65mm,C2866750,SMT extended,POPULATE,"VDD from switched HB_3V3; channels 1/2 carry SCL/SDA; R84 disables both used channels by default"
EXACT_CANDIDATE,U8,1,Four-channel active-high tri-state fan buffer,SN74LVC126A,Texas Instruments,SN74LVC126APWR,Package_SO:TSSOP-14_4.4x5mm_P0.65mm,C7815,SMT extended,POPULATE,"R105 leaves all 2N7002 sinks off; verify float-PWM full-speed behavior with the exact fan"
EXACT_CANDIDATE,U12,1,Independent gated hashboard reset buffer,SN74LVC1G125,Texas Instruments,SN74LVC1G125DBVR,Package_TO_SOT_SMD:SOT-23-5,C23654,SMT extended,POPULATE,"R89 is the mandatory 10k active-low OE pullup; default S21 assembly leaves R90 open/DNP"
EXACT_CANDIDATE,"Q1,Q2,Q3,Q4",4,Fan open-drain PWM sinks,2N7002,Nexperia or approved,2N7002,Package_TO_SOT_SMD:SOT-23,C8545,SMT basic,POPULATE,"R200/R203/R206/R209 are gate pulldowns; drain connects to each fan PWM line"
PROVISIONAL,"Q5,Q6",2,Parallel high-side fan-input reverse-polarity FETs,-30 V P-channel,Diodes Incorporated,DMP3013SFV-7,ChainAxe:PowerDI3333-8_DMP3013SFV,C264098,SMT extended,SELECT_BEFORE_RELEASE,"Use exact Diodes Type-UX mapping; validate paste, SOA, current sharing, Rds(on), copper, and simultaneous fan startup/stall thermals"
EXACT_CANDIDATE,ZD1,1,Fan-input MOSFET gate clamp,12 V Zener,onsemi,BZX84C12LT1G,Package_TO_SOT_SMD:SOT-23,C82475,SMT extended,SELECT_BEFORE_RELEASE,"Pin 1 anode to gate; pin 2 NC; pin 3 cathode to protected FAN_12V; validate dissipation and transients"
EXACT_CANDIDATE,U9,1,USB low-capacitance ESD,USBLC6-2SC6,STMicroelectronics,USBLC6-2SC6,Package_TO_SOT_SMD:SOT-23-6,C7519,SMT extended,POPULATE,"Place immediately behind the USB receptacle"
EXACT_CANDIDATE,"U10,U11,U13",3,Cable-side 3.3 V ESD array,TPD4E05U06,Texas Instruments,TPD4E05U06DQAR,ChainAxe:TI_DQA0010A_USON10_2.5x1.0_P0.5,C138714,SMT extended,POPULATE,"TI DQA0010A map and land: shunts 1/2/4/5; enlarged GND 3/8; NC 6/7/9/10; verify pin 1 at J10"
PROVISIONAL,"D1,D2,D3",3,Logic-source OR Schottky,1 A 40 V,Multiple,SS14,Diode_SMD:D_SMA,TBD,SMT,POPULATE,"D1 gives J6 reverse blocking; D2 is JP1-qualified FAN_12V; D3 is USB_VBUS; select exact MPN/LCSC and verify AP64501 headroom"
PROVISIONAL,D4,1,Protected fan-bus TVS,13 V standoff starting point,Multiple,SMBJ13A,Diode_SMD:D_SMB,TBD,SMT,SELECT_BEFORE_RELEASE,"Coordinate standoff and clamp energy with the exact 12 V fans and upstream fuse; J1 is not a 15 V fan input"
PROVISIONAL,D5,1,Logic-input bidirectional TVS,18 V standoff starting point,Multiple,SMBJ18CA,Diode_SMD:D_SMB,TBD,SMT,SELECT_BEFORE_RELEASE,"Bidirectional part at J6; verify pulse energy and clamping before release"
PROVISIONAL,J30,1,USB-C USB2 receptacle,USB4105-GF-A,Global Connector Technology,USB4105-GF-A,ChainAxe:USB4105-GF-A,C2988369,SMT extended,STOP_ORDER,"STOP-ORDER until first-article fit check: project-local footprint vendors the official KiCad 8.0.9/GCT geometry with all contacts, THT shell stakes, and NPTH locating pegs"
PROVISIONAL,J10,1,Bitmain hashboard data connector,2x9 2.00 mm right-angle,HCTL,PM200-2-09-W-4.3,ChainAxe:PM200-2-09-W-4.3_THT,C3012192,THT/manual,HAND_INSTALL,"18 physical positions; pins 1-16 used and 17-18 NC; project-local drawing-derived footprint still needs mating-face orientation and real-cable fit checks"
EXACT_CANDIDATE,J1,1,High-current fan supply input,2x3 keyed THT,Molex,0455580003,ChainAxe:0455580003_THT,C492365,THT/manual,HAND_INSTALL,"Regulated 12 V only; project-local footprint follows Molex SD-45558-001 contact and peg geometry; verify circuit-1 orientation and fit a real connector"
TBD,J6,1,Low-current controller supply input,2-pin keyed 18-24 AWG,TBD,TBD,Connector_Molex:Molex_Micro-Fit_3.0_43650-0200_1x02_P3.00mm_Horizontal,TBD,THT/manual,STOP_ORDER,"STOP-ORDER: accepts 12-15 V for logic only; current Micro-Fit footprint is a placeholder until an exact keyed connector and mate are selected"
EXACT_CANDIDATE,"J2,J3,J4,J5",4,AntHat-style four-wire fan connectors,Keyed 2x2 nominal 4.2 mm pitch,Molex,0353180420,ChainAxe:0353180420_THT,C54909,THT/manual,HAND_INSTALL,"Silk G/12/T/P; project-local footprint follows Molex SD-35318 4.2 x 5.5 mm pattern; verify key, circuit view, and real fan harness"
TBD,JP1,1,Optional fan-to-logic feed,Open solder jumper,N/A,N/A,Jumper:SolderJumper-2_P1.3mm_Open_Pad1.0x1.5mm,N/A,Manual,DNP,"Fit only when J1 is verified regulated 12 V; feeds FAN_12V through D2 and never bypasses the diode"
TBD,"SW1,SW2",2,BOOT and RESET buttons,Momentary NO,TBD,TBD,Button_Switch_SMD:SW_SPST_CK_RS282G05A3,TBD,SMT,STOP_ORDER,"STOP-ORDER: schematic uses the CK RS282G05A3 footprint; prior CS1213AGF260/C5578986 pairing is not footprint-verified and is removed from the JLC template"
EXACT_CANDIDATE,R60,1,Fan-input reverse-protection gate resistor,12k 1%,UNI-ROYAL,0402WGF1202TCE,Resistor_SMD:R_0402_1005Metric,C25752,SMT basic,SELECT_BEFORE_RELEASE,"Q5/Q6 gate pull; validate with ZD1 and final FET topology"
EXACT_CANDIDATE,"R50,R80,R83,R84,R105,R106,R107,R108,R109,R200,R203,R206,R209",13,Hardware safe-state pulls,100k 1%,UNI-ROYAL,0402WGF1003TCE,Resistor_SMD:R_0402_1005Metric,C25741,SMT basic,POPULATE,"U5 off; U6 off; PLUG defined; U7 off; fan arm off; R106-R109 define U8 inputs low until EMC2305 push-pull configuration; four fan gates off"
PROVISIONAL,R70,1,Rail-monitor divider top,100k 1%,UNI-ROYAL,0402WGF1003TCE,Resistor_SMD:R_0402_1005Metric,C25741,SMT basic,POPULATE,"With R71 and C70; validate ADC full-scale against the selected monitored rail"
PROVISIONAL,"R91,R92",2,Optional hashboard reset bias pads,100k starting value,UNI-ROYAL,0402WGF1003TCE,Resistor_SMD:R_0402_1005Metric,C25741,SMT basic,DNP,"Mutually exclusive reset bias-up/down options; default S21-safe assembly leaves both open"
EXACT_CANDIDATE,"R89,R110,R111",3,Reset-OE and MCU EN/BOOT pullups,10k 1%,UNI-ROYAL,0402WGF1002TCE,Resistor_SMD:R_0402_1005Metric,C25744,SMT basic,POPULATE,"R89 disables U12; R110 is ESP EN pullup; R111 is BOOT pullup"
PROVISIONAL,R51,1,Hashboard 3.3 V quick-output-discharge link,100 ohm 1%,Multiple,TBD,Resistor_SMD:R_0402_1005Metric,TBD,SMT,POPULATE,"VOUT to TPS22917 QOD; J10 pin 16 must never be externally driven"
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

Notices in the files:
boards/chainaxe/chainaxe.kicad_sch:
Derived from skot/bitcrane (GPL-3.0) and bitaxeorg/BitaxeGT (CERN-OHL-S-2.0)
parts and their libraries:
GCT USB4105-GF-A exact official KiCad 8.0.9 manufacturer-drawing-derived geometry; four conductive shell stakes share S1; includes two 0.65 mm NPTH locating pegs. Vendored from KiCad Connector_USB under CC-BY-SA 4.0; first-article fit check required.
